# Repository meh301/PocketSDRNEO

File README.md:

# **Pocket SDR - An Open-Source GNSS SDR, ver. 2.1 NEO**

## **This project is now archived**
The NEO variant of the v2.1 PocketSDR was only meant to be a short-term solution for increasing international interest in the open source project. The official PocketSDR has now been updated to include USB-C, as well as several design improvements. Please refer to the official Github: https://github.com/tomojitakasu/PocketSDR

---

The NEO* variant of Professor 高須知二 (Tomoji Takasu)'s PocketSDR replaces the micro-B connector with type-C, fixes the LDO routing, adds an 0603 100 Ohm resistor at the output of the RF power divider as per the datasheet, and finally provides the option of either using a pin header or a Littlefuse MICROSMD010 for antenna power delivery.

Please note that due to the use of a type-C connector, the dimensions of the board are slightly larger than the original design.

## **Overview**

Pocket SDR is an open-source GNSS (Global Navigation Satellite System) receiver
based on SDR (software defined radio) technology. It consists of a RF front-end
device, some utilities for the device and GNSS-SDR APs (application programs)
written in Python and C. It supports almost all signals for GPS, GLONASS,
Galileo, QZSS, BeiDou, NavIC and SBAS.

The RF front-end device consists of 2 CH Maxim MAX2771 GNSS RF front-end IC
(LNA, mixer, filter, ADC, frequency synthesizer) and Cypress EZ-USB FX2LP USB
2.0 controller to connect to host PCs. The front-end CH1 is dedicated for GNSS
L1 band (1525 - 1610 MHz) and CH2 is for GNSS L2/L5/L6 band (1160 - 1290 MHz).
The frequency of the reference oscillator (TCXO) is 24.000 MHz and ADC sampling
frequency can be configured up to 24 MHz.

Pocket SDR contains some utility programs for the RF front-end device to
configure the device, capture and dump the digitized IF (inter-frequency) data.
These supports Windows, Linux and other environments.

Pocket SDR also provides GNSS-SDR APs to show the PSD (power spectrum density)
of captured IF data, search the GNSS signals, track these signals and decode
navigation data in them. The supported GNSS signals are as follows. These APs
are written in Python by very compact way. They are easily modified by users
to add user's unique algorithms.

GPS: L1C/A, L1CP, L1CD, L2CM, L5I, L5Q, GLONASS: L1C/A, L2C/A, L3OCD, L3OCP,
Galileo: E1B, E1C, E5aI, E5aQ, E5bI, E5bQ, E6B, E6C, QZSS: L1C/A, L1C/B, L1CP,
L1CD, L1S, L2CM, L5I, L5Q, L5SI, L5SQ, L6D, L6E, BeiDou: B1I, B1CP, B1CD, B2I,
B2aD, B2aP, B2bI, B3I, NavIC: L5-SPS, SBAS: L1C/A, L5I, L5Q

The introduction of Pocket SDR is shown in the following slides.

T.Takasu, An Open Source GNSS SDR: Development and Application, IPNTJ Next GNSS
Technology WG, Feb 21, 2022
(https://gpspp.sakura.ne.jp/paper2005/IPNTJ_NEXTWG_202202.pdf)

---

## **Package Structure**

```
PocketSDR --+-- bin     Pocket SDR utilities and APs binary programs for Windows
            +-- app     Pocket SDR utilities and APs source programs
            +-- src     Pocket SDR library source programs
            +-- python  Pocket SDR Python scripts
            +-- lib     External library for utilities and APs
            +-- conf    Configuration files for device settings
            +-- driver  Windows driver for EZ-USB FX2LP/FX3 (cyusb3.sys) ([4])
            +-- doc     Documents (ref {1], [2])
            +-- FW      Firmware source programs and images
            |   +-- cypress  Cypress libraries for EZ-USB firmware development
            |                (ref [4])
            +-- HW      Pocket SDR RF frontend CAD data and parts list
            |           (*.brd and *.sch are for Eagle, *.f3d is for Fusion 360)
            +-- image   Image files for documents
            +-- sample  Sample digital IF data captured by Pocket SDR
            +-- test    Test codes
```

---

## **Installation for Windows**

- Extract PocketSDR.zip to an appropriate directory <install_dir>.

- Attach Pocket SDR RF frontend to PC via USB cable.

- Install USB driver (CYUSB) for Pocket SDR RF frontend according to
  PocketSDR\driver\readme.txt.

- Add the Pocket SDR binary programs path (<install_dir>\PocketSDR\bin) to
  the command search path (Path) of Windows environment variables.

- Add the Pocket SDR Python scripts path (<install_dir>\PocketSDR\python) to
  the command search path (Path) of Windows environment variables.

- To rebuild the binary programs, you need MinGW64 and libusb-1.0 library.
  Refer MSYS2 (https://www.msys2.org/) for details.

- In MinGW64 environment, you need fftw3 library. To install fftw3 library.

```
    $ pacman -S mingw-w64-x86_64-fftw
```

---

## **Installation for Linux**

- Extract PocketSDR.zip to an appropriate directory <install_dir>.

```
    $ unzip PocketSDR.zip
```

- Install libusb-1.0 developtment package. For Ubuntu:

```
    $ sudo apt install libusb-1.0-0-dev
```

- Install libfftw3 developtment package. For Ubuntu:

```
    $ sudo apt install libfftw3-dev
```

- Move to the library directory, build libraries.

```
    $ cd <install_dir>/lib/build
    $ make
    $ make install
```

- Move to the source program directory, build utilities and APs.

```
    $ cd <install_dir>/app
    $ make
    $ make install
```

- Add the Pocket SDR binary programs path (<install_dir>/PocketSDR/bin) to
  the command search path.

- Usually you need to have root permission to access USB devices. So you add
  sudo to execute pocket_conf, pocket_dump like:

```
   $ sudo pocket_conf ../conf/pocket_L1L6_12MHz.conf
   $ sudo pocket_dump -t 10 ch1.bin ch2.bin
```

---

## **Utility Programs for RF frontend**

Pocket SDR contains the following utility programs.

- **pocket_conf**: SDR device configurator
- **pocket_scan**: Scan and list USB Devices
- **pocket_dump**: Capture and dump digital IF data of SDR device

For details, refer comment lines in src/pocket_conf.c, src/pocket_scan.c,
src/pocket_dump.c.

---

## **GNSS-SDR APs (Application Programs)**

Pocket SDR contains the following application programs for GNSS-SDR.

- **pocket_psd.py** : Plot PSD and histgrams of digital IF data
- **pocket_acq.py** : GNSS signal acquisition in digital IF data
- **pocket_trk.py** : GNSS signal tracking and navigation data decoding in digital IF data
- **pocket_snap.py**: Snapshot positioning with digital IF data
- **pocket_plot.py**: Plot GNSS signal tracking log by pocket_trk.py
- **pocket_acq** : C-version of pocket_acq.py (w/o graph plots)
- **pocket_trk** : C-version of pocket_trk.py (w/o graph plots)

For details, refer comment lines in python/pocket_psd.py, python/pocket_acq.py,
python/pocket_trk.py, python/pocket_snap.py and python/pocket_plot.py. You need
Python 3, Numpy, Scipy and matplotlib to execute Python scripts. pocket_trk.py
uses external shared libraries of LIBFEC [5] and RTKLIB [6] in lib/ directory.
These were built for Windows (64bit) and Linux for x86_64 CPU.

---

## **Execution Examples of Utility Programs and GNSS-SDR APs**

```
    $ pocket_conf
    ...
    $ pocket_conf conf/pocket_L1L6_12MHz.conf
    Pocket SDR device settings are changed.

    $ pocket_dump -t 5 ch1.bin ch2.bin
      TIME(s)    T   CH1(Bytes)   T   CH2(Bytes)   RATE(Ks/s)
          5.0    I     59768832  IQ    119537664      11922.8

    $ pocket_psd.py ch1.bin -f 12 -h
    $ pocket_acq.py ch1.bin -f 12 -fi 3 -sig L1CA -prn 1-32,193-199
    PRN   1: SIG= L1CA, COFF=  0.12817 ms, DOP=  3500 Hz, C/N0= 37.4 dB-Hz
    PRN   2: SIG= L1CA, COFF=  0.85242 ms, DOP= -3500 Hz, C/N0= 36.8 dB-Hz
    PRN   3: SIG= L1CA, COFF=  0.39400 ms, DOP= -2000 Hz, C/N0= 37.0 dB-Hz
    PRN   4: SIG= L1CA, COFF=  0.96692 ms, DOP=  2000 Hz, C/N0= 44.7 dB-Hz
    ...
    $ pocket_acq.py ch1.bin -f 12 -fi 3 -sig L1CA -prn 26

    $ pocket_acq.py ch1.bin -f 12 -fi 3 -sig L1CA -prn 26 -3d

    $ pocket_acq.py ch2.bin -f 12 -sig L6D -prn 194 -p

    $ pocket_trk.py L1_24M.bin -prn 1-32 -f 24 -fi 6
	  TIME(s)   SIG  PRN  STATE   LOCK(s)  C/N0 (dB-Hz)        COFF(ms)   DOP(Hz)   ADR(cyc)  SYNC #NAV #ERR
	    1.550  L1CA    1   LOCK     1.539  42.5 ||||||||      0.8017699    3218.8     4949.3  ---     0    0
	    0.011  L1CA    2   IDLE     0.000   0.0               0.0000000       0.0        0.0  ---     0    0
	    0.011  L1CA    3   IDLE     0.000   0.0               0.0000000       0.0        0.0  ---     0    0
	    0.011  L1CA    4   IDLE     0.000   0.0               0.0000000       0.0        0.0  ---     0    0
	    0.011  L1CA    5   IDLE     0.000   0.0               0.0000000       0.0        0.0  ---     0    0
	    0.011  L1CA    6   IDLE     0.000   0.0               0.0000000       0.0        0.0  ---     0    0
	    1.550  L1CA    7   LOCK     1.539  45.7 ||||||||||    0.6995059     582.8      901.5  ---     0    0
	    1.550  L1CA    8   LOCK     1.539  47.6 |||||||||||   0.0733506    -777.2    -1196.8  ---     0    0
	    0.011  L1CA    9   IDLE     0.000   0.0               0.0000000       0.0        0.0  ---     0    0
	    1.550  L1CA   10   LOCK     1.539  38.6 |||||         0.8658548      -6.2       -9.4  ---     0    0
	...
    $ pocket_trk.py L1_24M.bin -prn 194 -sig L1CA -f 24 -fi 6 -log trk.log  -p
    ...
    $ pocket_trk.py L5_24M.bin -prn 13 -sig E5AI -f 24 -log trk.log -p -ts 0.2
    ...
```

---

## **Rebuild F/W and Write F/W Image to Pocket SDR RF frontend**

- Install Cypress EZ-USB FX2LP Development Kit (ref [4]) to a Windows PC. As
  default, it is installed to C:\Cypress and C:\Keil.

- Execute Keil uVision2 (C:\Keil\UV2\uv2.exe).

- Execute Menu Project - Open Project, select <install_dir>\PocketSDR\FW\pocket_fw.Uv2>
  and open the project.

- Execute Menu Project - Rebuild all target files and you can get a F/W image
  as <install_dir>\PocketSDR\FW\pocket_fw.iic.

- Attach Pocket SDR RF frontend via USB cable to the PC.

- Execute USB Control Center (C:\Cypress\USB\CY3684_EZ-USB_FX2LP_DVK\1.1\Windows Applications\
  c_sharp\controlcenter\bin\Release\CyControl.exe).

- Select Cypress FX2LP Sample Device, execute menu Program - FX2 - 64KB EEPROM,
  select the F/W image <install_dir>\PocketSDR\FW\pocket_fw.iic and open it.

- If you see "Programming succeeded." in status bar, the F/W is properly written
  to PocketSDR.

- To use utility programs for Pocket SDR, you need to reinstall WinUSB driver for
  Pocket SDR. Refer "Installation for Windows" above.

---

## **References**

[1] Maxim integrated, MAX2771 Multiband Universal GNSS Receiver, July 2018

[2] Cypress, EZ-USB FX2LP USB Microcontroller High-Speed USB Peripheral
Controller, Rev. AB, December 6, 2018

[3] (deleted)

[4] Cypress, CY3684 EZ-USB FX2LP Development Kit
(https://www.cypress.com/documentation/development-kitsboards/cy3684-ez-usb-fx2lp-development-kit)

[5] https://github.com/quiet/libfec

[6] https://github.com/tomojitakasu/RTKLIB

---

## **History**

- 2021-10-20 0.1 1st draft version
- 2021-10-25 0.2 Add Rebuild F/W and Write F/W Image to PocketSDR
- 2021-12-01 0.3 Add and modify Python scripts
- 2021-12-25 0.4 Add and modify Python scripts
- 2022-01-05 0.5 Fix several problems.
- 2022-01-13 0.6 Add and modify Python scripts
- 2022-02-15 0.7 Improve performance, Add some Python scripts.
- 2022-07-08 0.8 Add C-version of pocket_acq.py and pocket_trk.py.

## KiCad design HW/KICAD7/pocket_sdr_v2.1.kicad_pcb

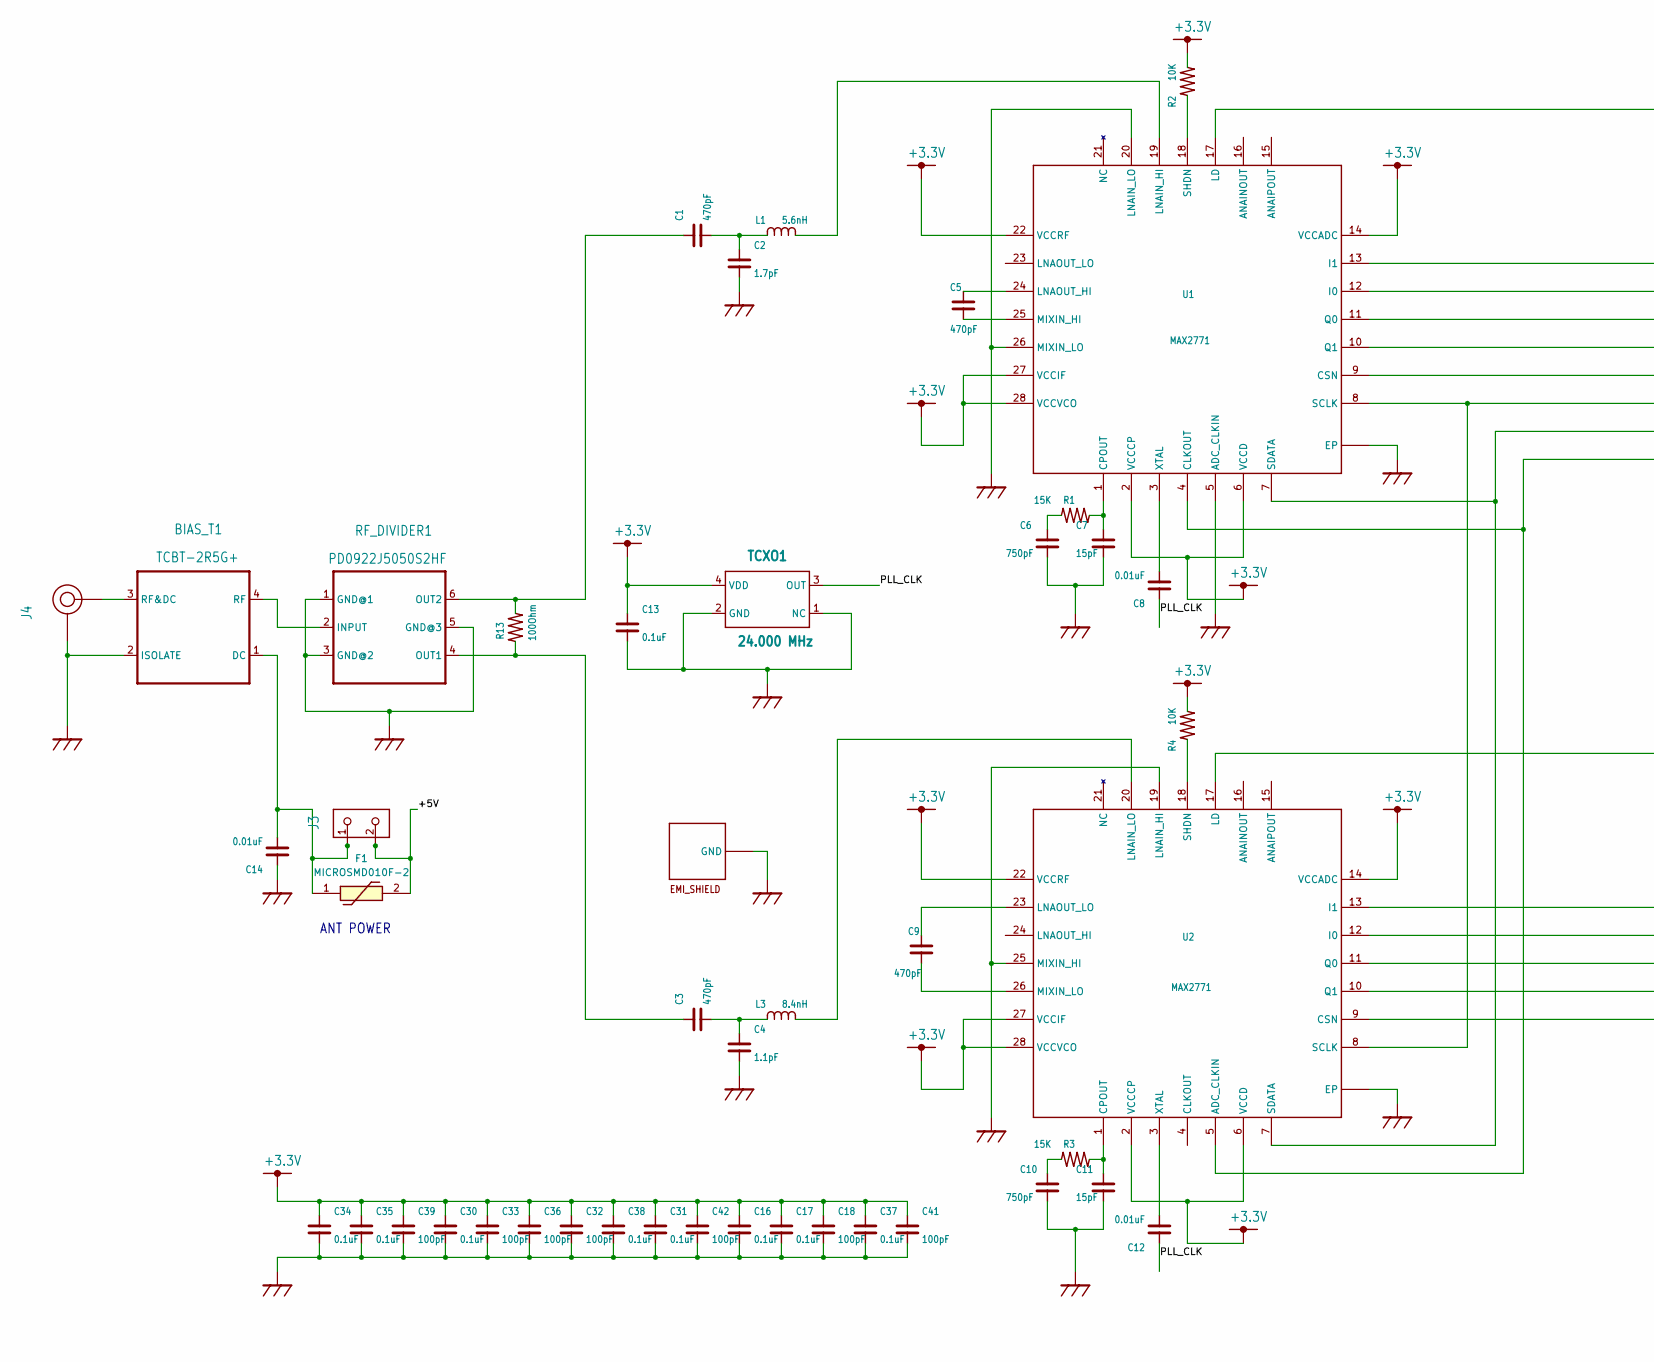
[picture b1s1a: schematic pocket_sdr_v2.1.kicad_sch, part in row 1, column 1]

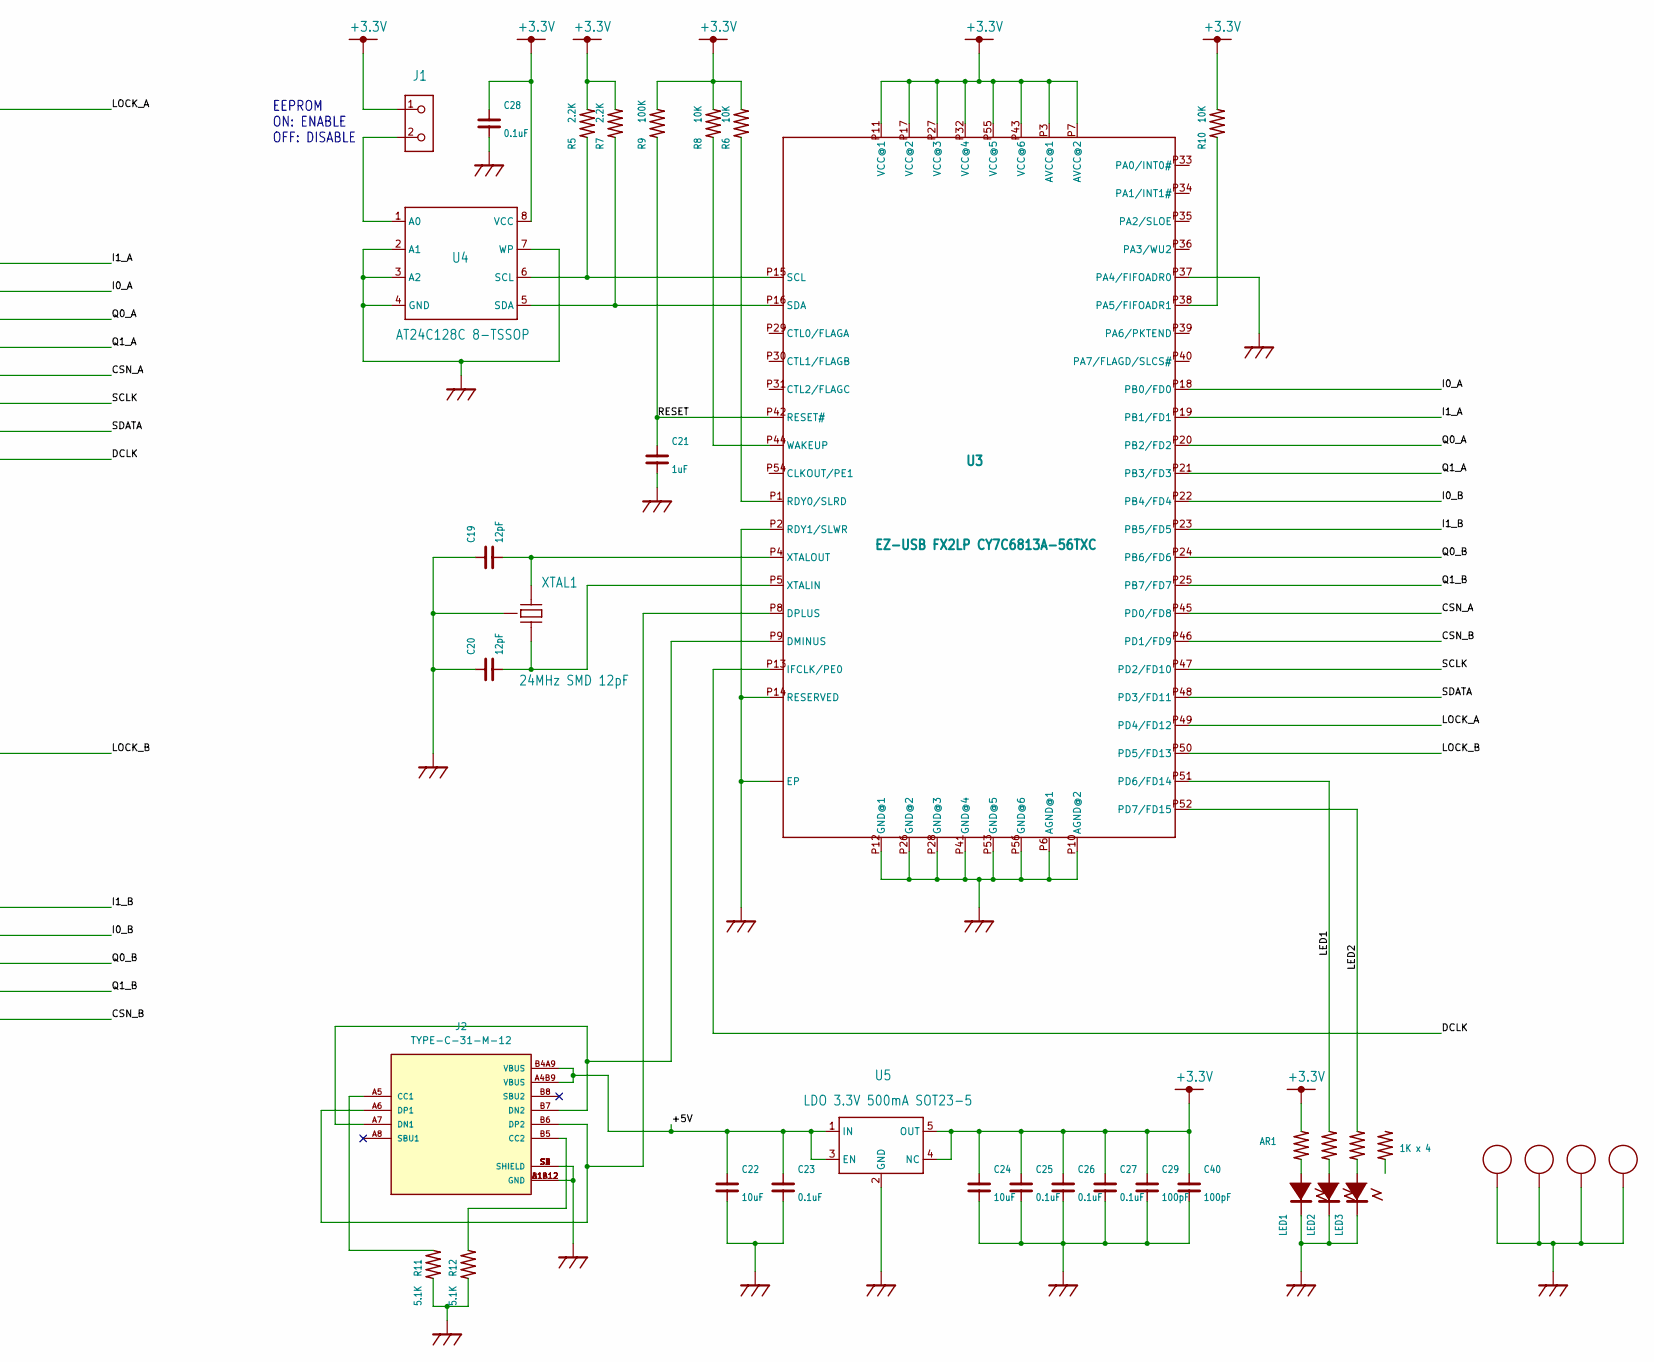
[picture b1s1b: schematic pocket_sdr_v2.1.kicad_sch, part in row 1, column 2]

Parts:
AR1: 1K x 4; EXB28V
BIAS_T1: TCBT-2R5G+; BIAS_T
C1, C3, C5, C9: 470pF; C1005
C2: 1.7pF; C1005
C4: 1.1pF; C1005
C6, C10: 750pF; C1005
C7, C11: 15pF; C1005
C8, C12, C14: 0.01uF; C1005
C13, C16, C17, C23, C25, C26, C27, C28, C30, C31, C34, C35, C37, C38: 0.1uF; C1005
C18, C29, C32, C33, C36, C39, C40, C41, C42: 100pF; C1005
C19, C20: 12pF; C1005
C21: 1uF; C1005
C22, C24: 10uF; C3225
F1: MICROSMD010F-2; MICROSMD175F2; Manufacturer_Part_Number MICROSMD010F-2; Mouser Part Number 650-MICROSMD010F-2
J1, J3: PIN HEADER 2MM 2P; PINH-2MM-2P
J2: TYPE-C-31-M-12; HRO_TYPE-C-31-M-12; PARTREV A
J4: SMA JACK EDGE MNT; SMA-ANG
L1: 5.6nH; C1608
L3: 8.4nH; C1608
LED1: LED1608 GREEN; LED_1608
LED2, LED3: LED1608 BLUE; LED_1608
R1, R3: 15K; C1005
R2, R4, R6, R8, R10: 10K; C1005
R5, R7: 2.2K; C1005
R9: 100K; C1005
R11, R12: 5.1K; C1005
R13: 100Ohm; C_0603_1608Metric
RF-SHEILD-CASE1: BMI-S-202-F BMI-S-202-C; BMI-S-202
RF_DIVIDER1: PD0922J5050S2HF; RF_DIV
TCXO1: 24.000 MHz; TCXO
U1, U2: MAX2771; TQFN28
U3: EZ-USB FX2LP CY7C6813A-56TXC; QFN56
U4: AT24C128C 8-TSSOP; TSSOP_8P
U5: LDO 3.3V 500mA SOT23-5; SOT23
XTAL1: 24MHz SMD 12pF; XTAL_SMD

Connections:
+3.3V: AR1.2, C13.1, C16.1, C17.1, C18.1, C24.P$1 (1), C25.1, C26.1, C27.1, C28.1, C29.1, C30.1, C31.1, C32.1, C33.1, C34.1, C35.1, C36.1, C37.1, C38.1, C39.1, C40.1, C41.1, C42.1, J1.1, R2.2, R4.2, R5.2, R6.2, R7.2, R8.2, R9.2, R10.2, TCXO1.4 (VDD), U1.2 (VCCCP), U1.6 (VCCD), U1.14 (VCCADC), U1.22 (VCCRF), U1.27 (VCCIF), U1.28 (VCCVCO), U2.2 (VCCCP), U2.6 (VCCD), U2.14 (VCCADC), U2.22 (VCCRF), U2.27 (VCCIF), U2.28 (VCCVCO), U3.P3 (AVCC@1), U3.P7 (AVCC@2), U3.P11 (VCC@1), U3.P17 (VCC@2), U3.P27 (VCC@3), U3.P32 (VCC@4), U3.P43 (VCC@6), U3.P55 (VCC@5), U4.8 (VCC), U5.4 (NC), U5.5 (OUT)
/+5V: C22.P$1 (1), C23.1, F1.2, J2.A4B9 (VBUS), J2.B4A9 (VBUS), J3.2, U5.1 (IN), U5.3 (EN)
/CSN_A: U1.9 (CSN), U3.P45 (PD0/FD8)
/CSN_B: U2.9 (CSN), U3.P46 (PD1/FD9)
/DCLK: U1.4 (CLKOUT), U2.5 (ADC_CLKIN), U3.P13 (IFCLK/PE0)
/I0_A: U1.12 (I0), U3.P18 (PB0/FD0)
/I0_B: U2.12 (I0), U3.P22 (PB4/FD4)
/I1_A: U1.13 (I1), U3.P19 (PB1/FD1)
/I1_B: U2.13 (I1), U3.P23 (PB5/FD5)
/LED1: AR1.4, U3.P51 (PD6/FD14)
/LED2: AR1.6, U3.P52 (PD7/FD15)
/LOCK_A: U1.17 (LD), U3.P49 (PD4/FD12)
/LOCK_B: U2.17 (LD), U3.P50 (PD5/FD13)
/PLL_CLK: C8.1, C12.1, TCXO1.3 (OUT)
/Q0_A: U1.11 (Q0), U3.P20 (PB2/FD2)
/Q0_B: U2.11 (Q0), U3.P24 (PB6/FD6)
/Q1_A: U1.10 (Q1), U3.P21 (PB3/FD3)
/Q1_B: U2.10 (Q1), U3.P25 (PB7/FD7)
/RESET: C21.1, R9.1, U3.P42 (RESET#)
/SCLK: U1.8 (SCLK), U2.8 (SCLK), U3.P47 (PD2/FD10)
/SDATA: U1.7 (SDATA), U2.7 (SDATA), U3.P48 (PD3/FD11)
GND: BIAS_T1.2 (ISOLATE), C2.1, C4.2, C6.2, C7.2, C10.2, C11.2, C13.2, C14.1, C16.2, C17.2, C18.2, C19.1, C20.1, C21.2, C22.P$2 (2), C23.2, C24.P$2 (2), C25.2, C26.2, C27.2, C28.2, C29.2, C30.2, C31.2, C32.2, C33.2, C34.2, C35.2, C36.2, C37.2, C38.2, C39.2, C40.2, C41.2, C42.2, J2.A1B12 (GND), J2.B1A12 (GND), J2.S1 (SHIELD), J2.S2 (SHIELD), J2.S3 (SHIELD), J2.S4 (SHIELD), J4.P2 (GND), J4.P3 (GND), J4.P4 (GND), J4.P5 (GND), LED1.2, LED2.2, LED3.2, R11.1, R12.1, RF-SHEILD-CASE1.P1 (GND), RF-SHEILD-CASE1.P2 (GND), RF-SHEILD-CASE1.P3 (GND), RF-SHEILD-CASE1.P4 (GND), RF-SHEILD-CASE1.P5 (GND), RF-SHEILD-CASE1.P6 (GND), RF-SHEILD-CASE1.P7 (GND), RF-SHEILD-CASE1.P8 (GND), RF-SHEILD-CASE1.P9 (GND), RF-SHEILD-CASE1.P10 (GND), RF-SHEILD-CASE1.P11 (GND), RF-SHEILD-CASE1.P12 (GND), RF_DIVIDER1.1 (GND@1), RF_DIVIDER1.3 (GND@2), RF_DIVIDER1.5 (GND@3), TCXO1.1 (NC), TCXO1.2 (GND), U1.5 (ADC_CLKIN), U1.20 (LNAIN_LO), U1.26 (MIXIN_LO), U1.C1 (EP), U1.C2 (EP), U1.C3 (EP), U1.C4 (EP), U1.EP, U1.V1 (EP), U1.V2 (EP), U1.V3 (EP), U1.V4 (EP), U1.V5 (EP), U1.V6 (EP), U1.V7 (EP), U1.V8 (EP), U1.V9 (EP), U2.19 (LNAIN_HI), U2.25 (MIXIN_HI), U2.C1 (EP), U2.C2 (EP), U2.C3 (EP), U2.C4 (EP), U2.EP, U2.V1 (EP), U2.V2 (EP), U2.V3 (EP), U2.V4 (EP), U2.V5 (EP), U2.V6 (EP), U2.V7 (EP), U2.V8 (EP), U2.V9 (EP), U3.EP1 (EP), U3.EP2 (EP), U3.EP3 (EP), U3.EP4 (EP), U3.EP5 (EP), U3.P2 (RDY1/SLWR), U3.P6 (AGND@1), U3.P10 (AGND@2), U3.P12 (GND@1), U3.P14 (RESERVED), U3.P26 (GND@2), U3.P28 (GND@3), U3.P37 (PA4/FIFOADR0), U3.P41 (GND@4), U3.P53 (GND@5), U3.P56 (GND@6), U3.P$1 (EP), U3.P$2 (EP), U3.P$3 (EP), U3.P$4 (EP), U3.P$5 (EP), U3.P$6 (EP), U3.P$7 (EP), U3.P$8 (EP), U3.P$9 (EP), U3.P$10 (EP), U3.P$11 (EP), U3.P$12 (EP), U3.P$13 (EP), U3.P$14 (EP), U3.P$15 (EP), U3.P$16 (EP), U3.P$17 (EP), U3.P$18 (EP), U3.P$19 (EP), U3.P$20 (EP), U4.2 (A1), U4.3 (A2), U4.4 (GND), U4.7 (WP), U5.2 (GND), XTAL1.P2 (GND), XTAL1.P4 (GND); also elsewhere on the board
unnamed: AR1.1, LED1.1 (+)
unnamed: AR1.3, LED2.1 (+)
unnamed: AR1.5, LED3.1 (+)
unnamed: BIAS_T1.1 (DC), C14.2, F1.1, J3.1
unnamed: BIAS_T1.3 (RF&DC), J4.P1 (RF)
unnamed: BIAS_T1.4 (RF), RF_DIVIDER1.2 (INPUT)
unnamed: J1.2, U4.1 (A0)
unnamed: J2.A5 (CC1), R11.2
unnamed: J2.B5 (CC2), R12.2
unnamed: J2.A7 (DN1), J2.B7 (DN2), U3.P9 (DMINUS)
unnamed: J2.A6 (DP1), J2.B6 (DP2), U3.P8 (DPLUS)
unnamed: C1.2, C2.2, L1.1
unnamed: L1.2, U1.19 (LNAIN_HI)
unnamed: C3.2, C4.1, L3.1
unnamed: L3.2, U2.20 (LNAIN_LO)
unnamed: C6.1, R1.1
unnamed: C7.1, R1.2, U1.1 (CPOUT)
unnamed: R2.1, U1.18 (SHDN)
unnamed: C10.1, R3.1
unnamed: C11.1, R3.2, U2.1 (CPOUT)
unnamed: R4.1, U2.18 (SHDN)
unnamed: R5.1, U3.P15 (SCL), U4.6 (SCL)
unnamed: R6.1, U3.P1 (RDY0/SLRD)
unnamed: R7.1, U3.P16 (SDA), U4.5 (SDA)
unnamed: R8.1, U3.P44 (WAKEUP)
unnamed: R10.1, U3.P38 (PA5/FIFOADR1)
unnamed: C3.1, R13.1, RF_DIVIDER1.4 (OUT1)
unnamed: C1.1, R13.2, RF_DIVIDER1.6 (OUT2)
unnamed: C5.1, U1.24 (LNAOUT_HI)
unnamed: C5.2, U1.25 (MIXIN_HI)
unnamed: C8.2, U1.3 (XTAL)
unnamed: C9.1, U2.23 (LNAOUT_LO)
unnamed: C9.2, U2.26 (MIXIN_LO)
unnamed: C12.2, U2.3 (XTAL)
unnamed: C20.2, U3.P5 (XTALIN), XTAL1.P3 (XTAL2)
unnamed: C19.2, U3.P4 (XTALOUT), XTAL1.P1 (XTAL1)

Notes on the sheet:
ANT POWER
EEPROM ON: ENABLE OFF: DISABLE

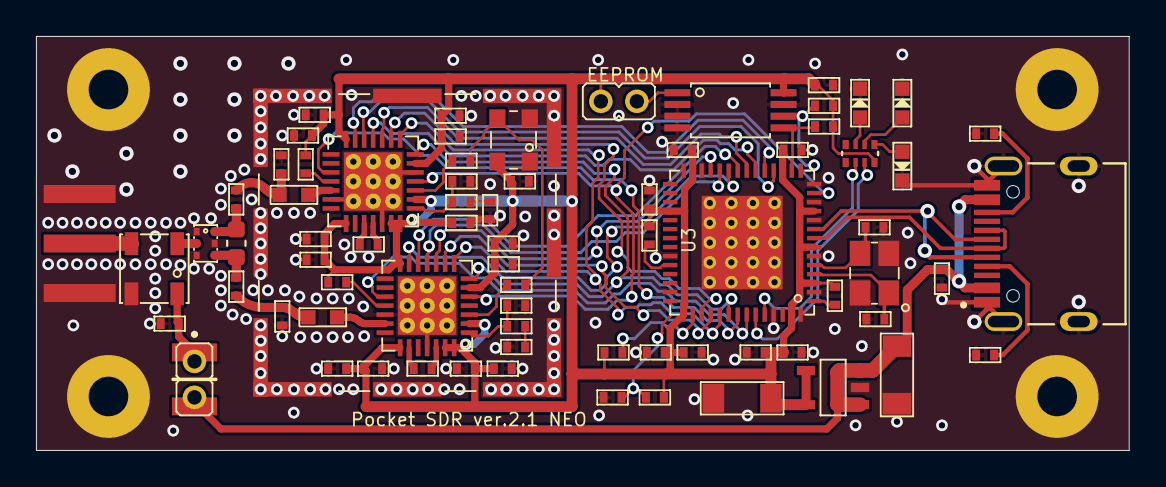
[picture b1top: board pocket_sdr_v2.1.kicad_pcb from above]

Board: 2 copper layers, 60.7 x 23.0 mm, 79 parts (0 on the bottom side), 58 nets.

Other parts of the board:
U$53, U$54, U$55, U$58: CPAD_2.2MM

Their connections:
GND: U$53.EP, U$54.EP, U$55.EP, U$58.EP; also elsewhere on the board

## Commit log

2023-12-21 Switch to KiCAD 7+
    Eagle is being discontinued in the future. For the NEO variant of PocketSDR (type-C), the Eagle version has been archived.
2023-12-21 Add BOM & Gerber
2023-12-21 Added NEO description & image
2023-12-21 added MICROSMD010 to list
2023-12-21 Switch to KiCAD 7+
2023-12-22 Switch to KiCAD 7+
    Updated board dimensions
2024-06-14 Archival announcement
